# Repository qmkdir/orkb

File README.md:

> [!CAUTION]
> PCB in active development, don't manufacture until files are released!

# ORCA KEYBOARD

ORCA is a 46 key column-staggered split keyboard with an aggresive stagger (especially the pinky) and a curved thumb cluster with an extra index finger key!

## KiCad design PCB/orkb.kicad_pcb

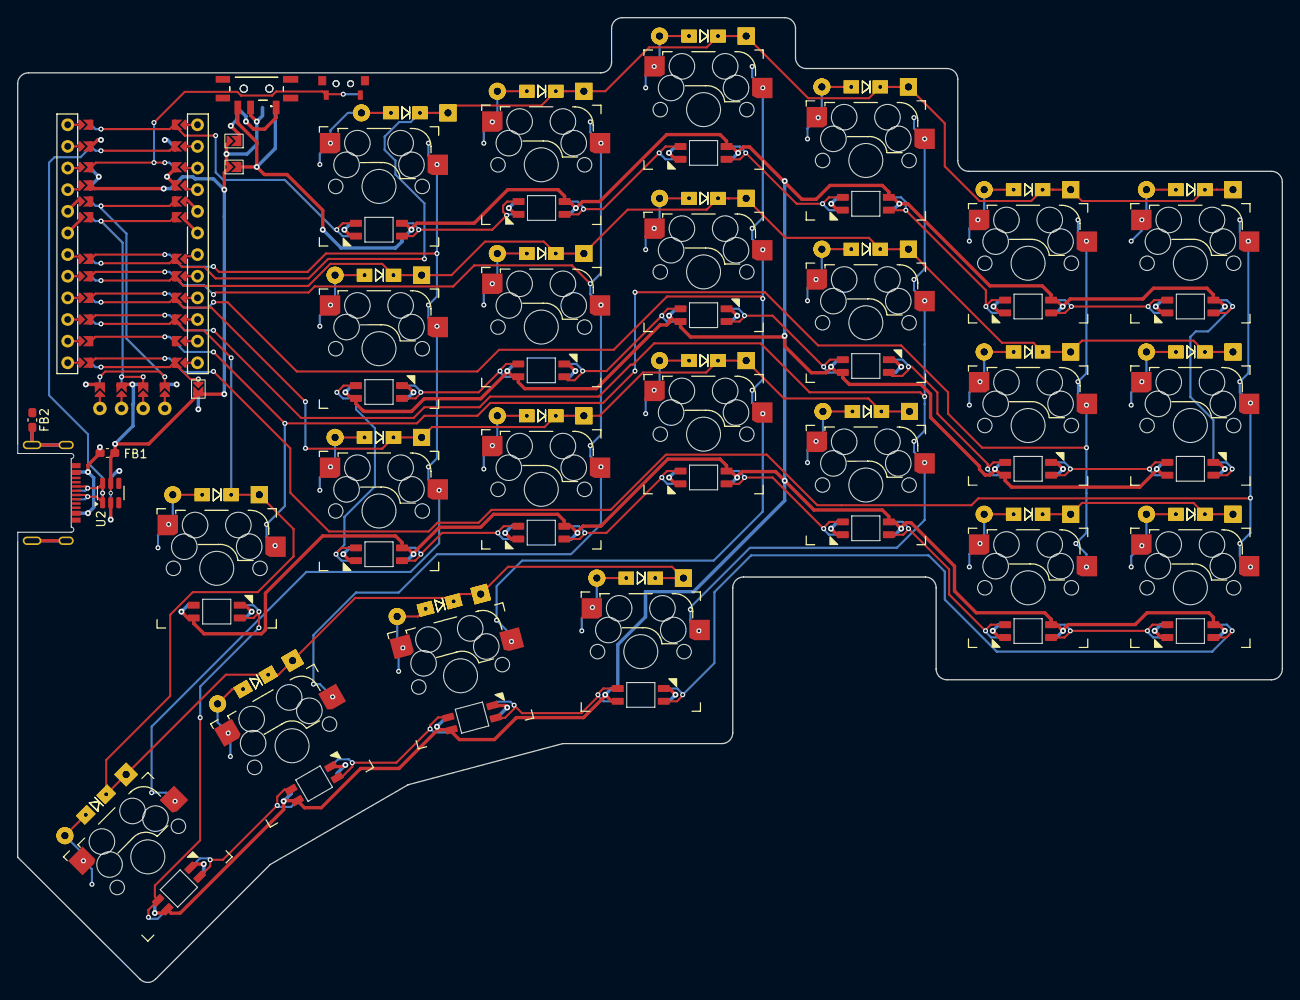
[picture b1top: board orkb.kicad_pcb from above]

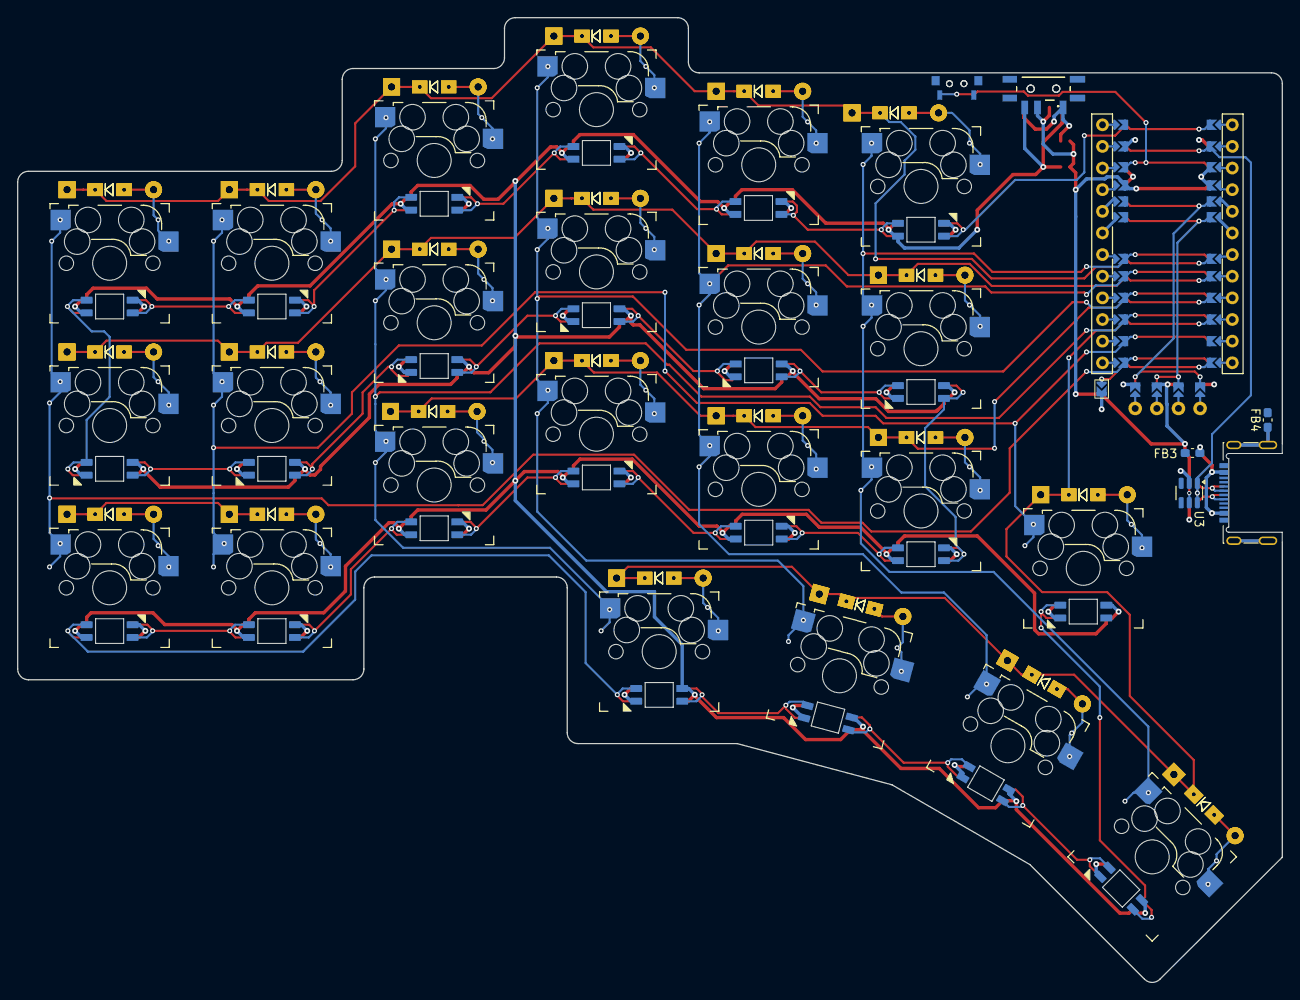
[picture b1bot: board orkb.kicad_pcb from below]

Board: 2 copper layers, 148.5 x 113.3 mm, 109 parts (61 on the bottom side), 67 nets.

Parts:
D1, D2, D3, D4, D5, D6, D7, D8, D9, D10, D11, D12, D13, D14, D15, D16, D17, D18, D19, D20, D21, D22, D23, D24, D25, D26, D27, D28, D29, D30, D31, D32, D33, D34, D35, D36, D37, D38, D39, D40, D41, D42, D43, D44, D45, D46: 1N4841/1N4148W; Diode_DO35_SOD123_Hybrid
FB1, FB2, FB3, FB4: FerriteBead; C_0603_1608Metric_Pad1.08x0.95mm_HandSolder
J1: USB_C_Receptacle_USB2.0; HRO-TYPE-C-31-M-13x_DOUBLESIDED_Molex-216990_GCT-USB45xx
JP1, JP2, JP3, JP4: Jumper_2_Open; Jumper_min_v2
LED1, LED2, LED3, LED4, LED5, LED6, LED7, LED8, LED9, LED10, LED11, LED12, LED13, LED14, LED15, LED16, LED17, LED18, LED19, LED20, LED21, LED22, LED23: SK6803MINI-E; MX_SK6812MINI-E_REVERSIBLE
P1: OLED; SSD1306-0.91-OLED-4pin-128x32_DOUBLESIDED
RES1, RES2: TS-A002_TactileSW; YTS-A002
SW1, SW2, SW3, SW4, SW5, SW6, SW7, SW8, SW9, SW10, SW11, SW12, SW13, SW14, SW15, SW16, SW17, SW18, SW19, SW20, SW21, SW22, SW23: MXHS; SW_MX_HotSwap_Reversible
SW24, SW25: MSK12C02
U1: ProMicro; ProMicro_Jumpers_V2
U2, U3: SRV05-4; SOT-23-6

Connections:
/PWR_GLOW: JP3.1 (A), SW24.NC, SW25.NC
/PWR_KEY: JP4.1 (A), LED1.1 (VDD), LED2.1 (VDD), LED3.1 (VDD), LED4.1 (VDD), LED5.1 (VDD), LED6.1 (VDD), LED7.1 (VDD), LED8.1 (VDD), LED9.1 (VDD), LED10.1 (VDD), LED11.1 (VDD), LED12.1 (VDD), LED13.1 (VDD), LED14.1 (VDD), LED15.1 (VDD), LED16.1 (VDD), LED17.1 (VDD), LED18.1 (VDD), LED19.1 (VDD), LED20.1 (VDD), LED21.1 (VDD), LED22.1 (VDD), LED23.1 (VDD), SW24.NO, SW25.NO
/VCC_LINK: FB1.1, FB3.1, J1.A4 (VBUS), J1.A9 (VBUS), J1.B4 (VBUS), J1.B9 (VBUS)
DATA: J1.A7 (D-), J1.B7 (D-), U1.2 (RX1/PD2), U2.1 (IO1), U2.6 (IO4), U3.1 (IO1), U3.6 (IO4)
GND: FB2.2, FB4.2, J1.A1 (GND), J1.A12 (GND), J1.B1 (GND), J1.B12 (GND), JP2.1 (A), LED1.3 (GND), LED2.3 (GND), LED3.3 (GND), LED4.3 (GND), LED5.3 (GND), LED6.3 (GND), LED7.3 (GND), LED8.3 (GND), LED9.3 (GND), LED10.3 (GND), LED11.3 (GND), LED12.3 (GND), LED13.3 (GND), LED14.3 (GND), LED15.3 (GND), LED16.3 (GND), LED17.3 (GND), LED18.3 (GND), LED19.3 (GND), LED20.3 (GND), LED21.3 (GND), LED22.3 (GND), LED23.3 (GND), P1.1 (GND), RES1.2, RES1.3, RES2.2, RES2.3, SW24.MP (GND), SW25.MP (GND), U1.3 (GND), U1.4 (GND), U1.23 (GND), U2.2 (VN), U3.2 (VN)
Hand: JP1.2 (B), JP2.2 (B), U1.12 (9/PB5)
LED: LED1.4 (DIN), U1.1 (TX0/PD3)
unnamed: D1.2 (A), D23.2 (A), SW1.2
unnamed: D2.2 (A), D24.2 (A), SW2.2
unnamed: D10.2 (A), D32.2 (A), SW10.2
unnamed: D11.2 (A), D33.2 (A), SW11.2
unnamed: D12.2 (A), D34.2 (A), SW12.2
unnamed: D13.2 (A), D35.2 (A), SW13.2
unnamed: D14.2 (A), D36.2 (A), SW14.2
unnamed: D15.2 (A), D37.2 (A), SW15.2
unnamed: D16.2 (A), D38.2 (A), SW16.2
unnamed: D17.2 (A), D39.2 (A), SW17.2
unnamed: D18.2 (A), D40.2 (A), SW18.2
unnamed: D19.2 (A), D41.2 (A), SW19.2
unnamed: D20.2 (A), D42.2 (A), SW20.2
unnamed: D21.2 (A), D43.2 (A), SW21.2
unnamed: D22.2 (A), D44.2 (A), SW22.2
unnamed: D3.2 (A), D25.2 (A), SW3.2
unnamed: D4.2 (A), D26.2 (A), SW4.2
unnamed: D5.2 (A), D27.2 (A), SW5.2
unnamed: D6.2 (A), D28.2 (A), SW6.2
unnamed: D7.2 (A), D29.2 (A), SW7.2
unnamed: D8.2 (A), D30.2 (A), SW8.2
unnamed: D9.2 (A), D31.2 (A), SW9.2
unnamed: D45.2 (A), D46.2 (A), SW23.2
unnamed: FB2.1, FB4.1, J1.S1 (SHIELD)
unnamed: LED1.2 (DOUT), LED2.4 (DIN)
unnamed: LED2.2 (DOUT), LED3.4 (DIN)
unnamed: LED3.2 (DOUT), LED4.4 (DIN)
unnamed: LED4.2 (DOUT), LED5.4 (DIN)
unnamed: LED5.2 (DOUT), LED6.4 (DIN)
unnamed: LED7.4 (DIN), LED8.2 (DOUT)
unnamed: LED8.4 (DIN), LED9.2 (DOUT)
unnamed: LED10.4 (DIN), LED11.2 (DOUT)
unnamed: LED9.4 (DIN), LED10.2 (DOUT)
unnamed: LED11.4 (DIN), LED12.2 (DOUT)
unnamed: LED6.2 (DOUT), LED12.4 (DIN)
unnamed: LED7.2 (DOUT), LED13.4 (DIN)
unnamed: LED13.2 (DOUT), LED14.4 (DIN)
unnamed: LED14.2 (DOUT), LED15.4 (DIN)
unnamed: LED15.2 (DOUT), LED16.4 (DIN)
unnamed: LED16.2 (DOUT), LED17.4 (DIN)
unnamed: LED17.2 (DOUT), LED18.4 (DIN)
unnamed: LED18.2 (DOUT), LED23.4 (DIN)
unnamed: LED19.4 (DIN), LED20.2 (DOUT)
unnamed: LED20.4 (DIN), LED21.2 (DOUT)
unnamed: LED21.4 (DIN), LED22.2 (DOUT)
unnamed: LED22.4 (DIN), LED23.2 (DOUT)
RESET: RES1.1, RES2.1, U1.22 (RST)
SCL: P1.3 (SCL), U1.6 (3/PD0)
SDA: P1.4 (SDA), U1.5 (2/PD1)
VCC: FB1.2, FB3.2, JP1.1 (A), JP3.2 (B), JP4.2 (B), P1.2 (VCC), SW24.COM, SW25.COM, U1.21 (VCC), U2.5 (VP), U3.5 (VP)
col0: SW1.1, SW7.1, SW13.1, SW19.1, U1.18 (A1/PF6)
col1: SW2.1, SW8.1, SW14.1, SW20.1, U1.17 (A0/PF7)
col2: SW3.1, SW9.1, SW15.1, SW21.1, U1.16 (15/PB1)
col3: SW4.1, SW10.1, SW16.1, SW22.1, U1.15 (14/PB3)
col4: SW5.1, SW11.1, SW17.1, SW23.1, U1.14 (16/PB2)
col5: SW6.1, SW12.1, SW18.1, U1.13 (10/PB6)
row0: D1.1 (K), D2.1 (K), D3.1 (K), D4.1 (K), D5.1 (K), D6.1 (K), D23.1 (K), D24.1 (K), D25.1 (K), D26.1 (K), D27.1 (K), D28.1 (K), U1.7 (4/PD4)
row1: D7.1 (K), D8.1 (K), D9.1 (K), D10.1 (K), D11.1 (K), D12.1 (K), D29.1 (K), D30.1 (K), D31.1 (K), D32.1 (K), D33.1 (K), D34.1 (K), U1.8 (5/PC6)
row2: D13.1 (K), D14.1 (K), D15.1 (K), D16.1 (K), D17.1 (K), D18.1 (K), D35.1 (K), D36.1 (K), D37.1 (K), D38.1 (K), D39.1 (K), D40.1 (K), U1.9 (6/PD7)
row3: D19.1 (K), D20.1 (K), D21.1 (K), D22.1 (K), D41.1 (K), D42.1 (K), D43.1 (K), D44.1 (K), D45.1 (K), D46.1 (K), U1.10 (7/PE6)

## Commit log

2024-07-07 init
    Initial commit
2024-07-08 Added MCU with reverse routing
    MCU routed for reverse PCB usage
    TODO:
    Fix GND and RESET pin connections
2024-07-12 Draft schematic components
    [Pending]
    Import to PCB
2024-07-12 Keyboard layout and switch positioning
2024-07-12 Keyboard layout + component placement
2024-07-15 First draft of routing of rows and columns
2024-07-23 Refactoring entire project
2024-07-23 Added extra index finger switch
2024-07-23 Updating layout
2024-07-23 Reset switch repositioning and labeling
2024-07-24 Changing layout and adding space for a three way switch
2024-07-24 Added support for LED in schematic
2024-07-24 Updated PCB with LED and switch
2024-07-25 Added underglow LED to schematic
2024-07-25 Added underglow LEDs to PCB
2024-07-26 LED double-sided routing for row0
2024-07-26 Added all LED reversible connections
2024-07-29 Initial column routing
2024-07-30 Rows and columns routed
2024-07-30 Row0 per key and under-glow RGB routing
2024-07-31 Removing under-glow LEDs (for now)
2024-07-31 Per key RBG, Switch column and row routing complete
2024-07-31 Corrected schematic connection of index & thumb cluster
2024-07-31 Initial complete routing of PCB
2024-07-31 Fixing column order and routing
2024-08-01 Fix column routing for index/thumb cluster
2024-08-01 Updating README and PCB image
2024-08-01 Refactoring project files
2024-08-01 Routing changes
2024-09-07 Sync
